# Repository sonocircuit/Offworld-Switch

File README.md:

# OFFWORLD/SWITCH

The OFFWORLD/SWITCH is a small device to switch the USB data lines of a device between two hosts (A and B).

I needed a small device to switch the usb connection between a Norns and Ansible. While designing I deceded to incorporate monome's idea of the [offworld-1 device](https://github.com/monome/offworld-1). A more appropriate name would be "WORLD/SELECTOR" as it only works as offworld when the jumper is in the center position.

## How to use
There are three miniUSB B connectors on the rear and one USB A connector on the side. The Datalines D+/D- of the USB A are switched between the two outer miniUSB B connectors (A and B) via switch. <br>
The center miniUSB B connector provides +5V only.

The miniUSB connector powering the device connected to the USB A can be selected via jumper. <br>
Top position A, middle position PWR and bottom position B.

## Future improvements

* replace the 6pin jumper with a three way switch. However, while testing, hotswiching the power source made Norns crash on several occations.

## Make your own

[Eagle files](https://github.com/sonoCircuits/Offworld-Switch/tree/master/OFFWORLD-SWITCH%20EAGLE%20FILES)

[Octopart BOM](https://octopart.com/bom-tool/UnnvVqt7)

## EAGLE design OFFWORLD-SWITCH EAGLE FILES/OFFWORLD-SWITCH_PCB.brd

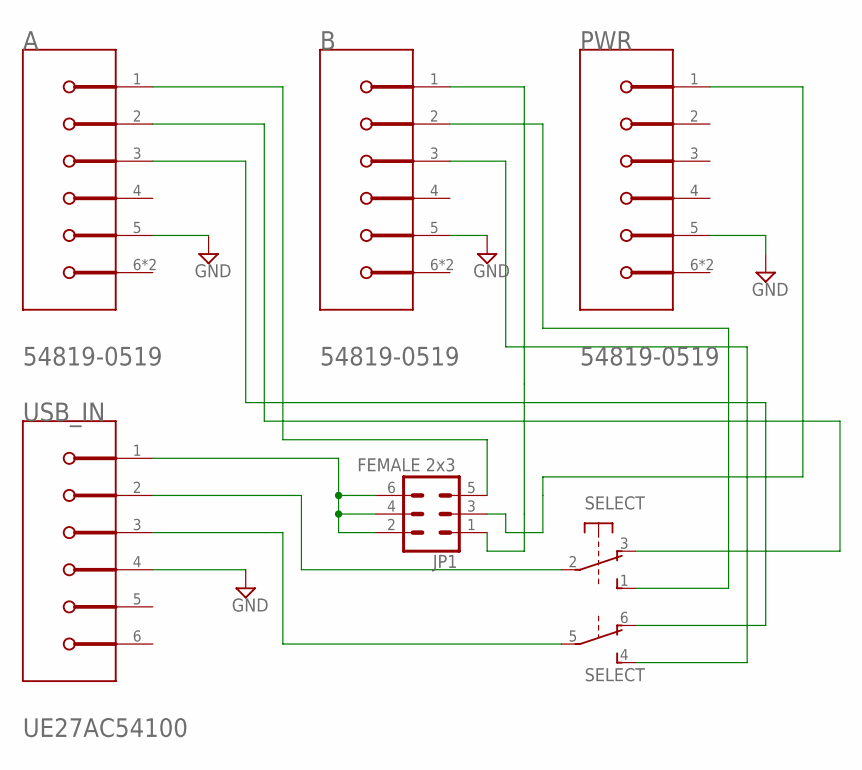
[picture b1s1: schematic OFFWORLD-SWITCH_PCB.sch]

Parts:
A: MOLEX_54819-0519MOLEX_54819-0519_0_0; MOLEX_54819-0519_0
B: MOLEX_54819-0519MOLEX_54819-0519_0_0; MOLEX_54819-0519_0
JP1: FEMALE 2x3; 2X3
PWR: MOLEX_54819-0519MOLEX_54819-0519_0_0; MOLEX_54819-0519_0
SELECT: 9450-2
USB_IN: AMPHENOL_UE27AC54100AMPHENOL_UE27AC54100_0_0; AMPHENOL_UE27AC54100_0

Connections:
GND: A.5 (GND), B.5 (GND), PWR.5 (GND), USB_IN.4
unnamed: JP1.2, JP1.4, JP1.6, USB_IN.1
unnamed: SELECT.2, USB_IN.2
unnamed: SELECT.5, USB_IN.3
unnamed: A.1 (VBUS), JP1.5
unnamed: JP1.3, PWR.1 (VBUS)
unnamed: B.1 (VBUS), JP1.1
unnamed: B.2 (D-), SELECT.1 (S)
unnamed: B.3 (D+), SELECT.4 (S)
unnamed: A.2 (D-), SELECT.3 (O)
unnamed: A.3 (D+), SELECT.6 (O)

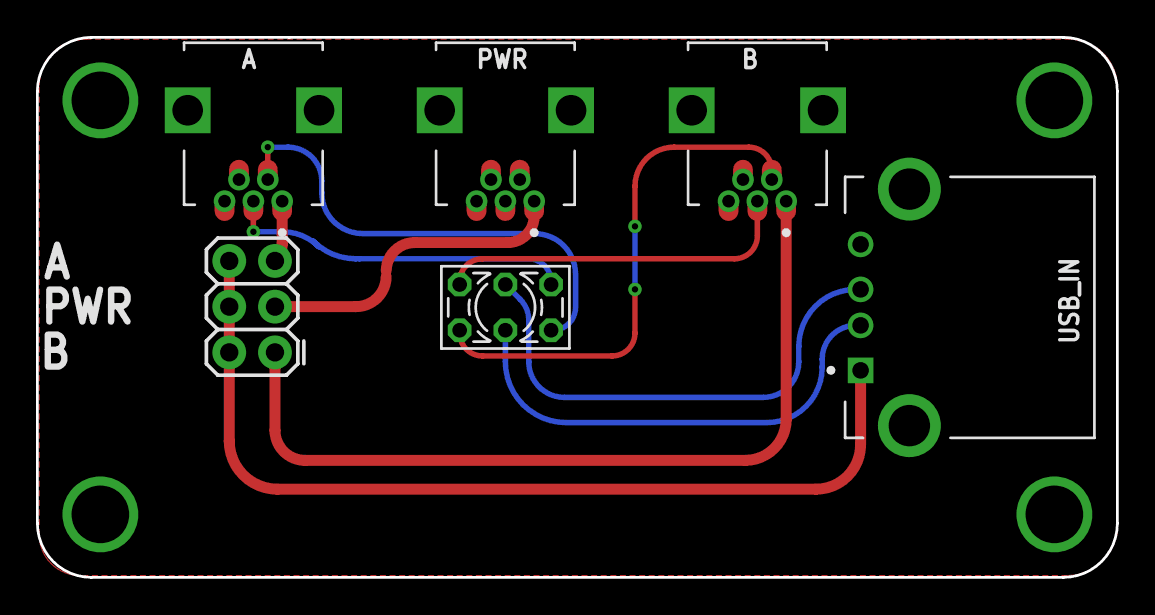
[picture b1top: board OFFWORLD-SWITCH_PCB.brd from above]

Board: 2 copper layers, 60.0 x 30.0 mm, 6 parts (0 on the bottom side), 11 nets.

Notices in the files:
parts and their libraries:
SparkFun-Connectors: Licensing: Creative Commons ShareAlike 4.0 International - https://creativecommons.org/licenses/by-sa/4.0
